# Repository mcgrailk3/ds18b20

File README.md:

# ds18b20

10 sensor PCB designed in KiCad for use with the DS18B20 sensors and 1Wire

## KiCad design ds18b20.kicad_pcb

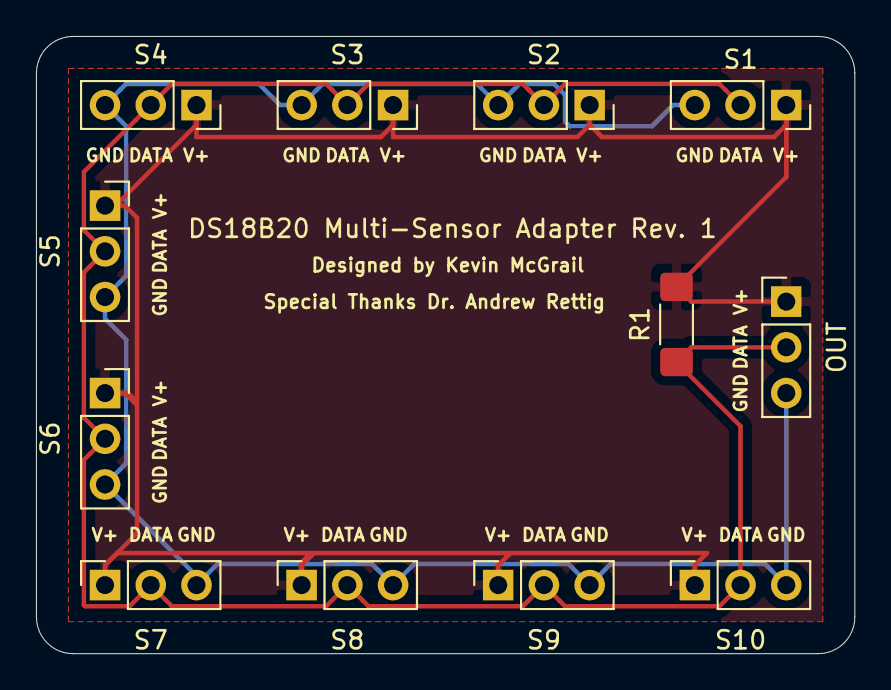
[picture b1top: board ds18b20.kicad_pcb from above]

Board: 2 copper layers, 45.5 x 34.3 mm, 12 parts (0 on the bottom side), 3 nets.

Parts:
J1: S4; PinSocket_1x03_P2.54mm_Vertical
J2: S5; PinSocket_1x03_P2.54mm_Vertical
J3: S3; PinSocket_1x03_P2.54mm_Vertical
J4: S2; PinSocket_1x03_P2.54mm_Vertical
J5: S1; PinSocket_1x03_P2.54mm_Vertical
J6: S9; PinSocket_1x03_P2.54mm_Vertical
J7: S6; PinSocket_1x03_P2.54mm_Vertical
J8: S7; PinSocket_1x03_P2.54mm_Vertical
J9: S8; PinSocket_1x03_P2.54mm_Vertical
J10: S10; PinSocket_1x03_P2.54mm_Vertical
J11: OUT; PinHeader_1x03_P2.54mm_Vertical
R1: 4.7k; R_1806_4516Metric_Pad1.57x1.80mm_HandSolder

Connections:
DATA: J1.2, J2.2, J3.2, J4.2, J5.2, J6.2, J7.2, J8.2, J9.2, J10.2, J11.2, R1.2
DC: J1.1, J2.1, J3.1, J4.1, J5.1, J6.1, J7.1, J8.1, J9.1, J10.1, J11.1, R1.1
GND: J1.3, J2.3, J3.3, J4.3, J5.3, J6.3, J7.3, J8.3, J9.3, J10.3, J11.3

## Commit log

2019-11-26 Initializing files
